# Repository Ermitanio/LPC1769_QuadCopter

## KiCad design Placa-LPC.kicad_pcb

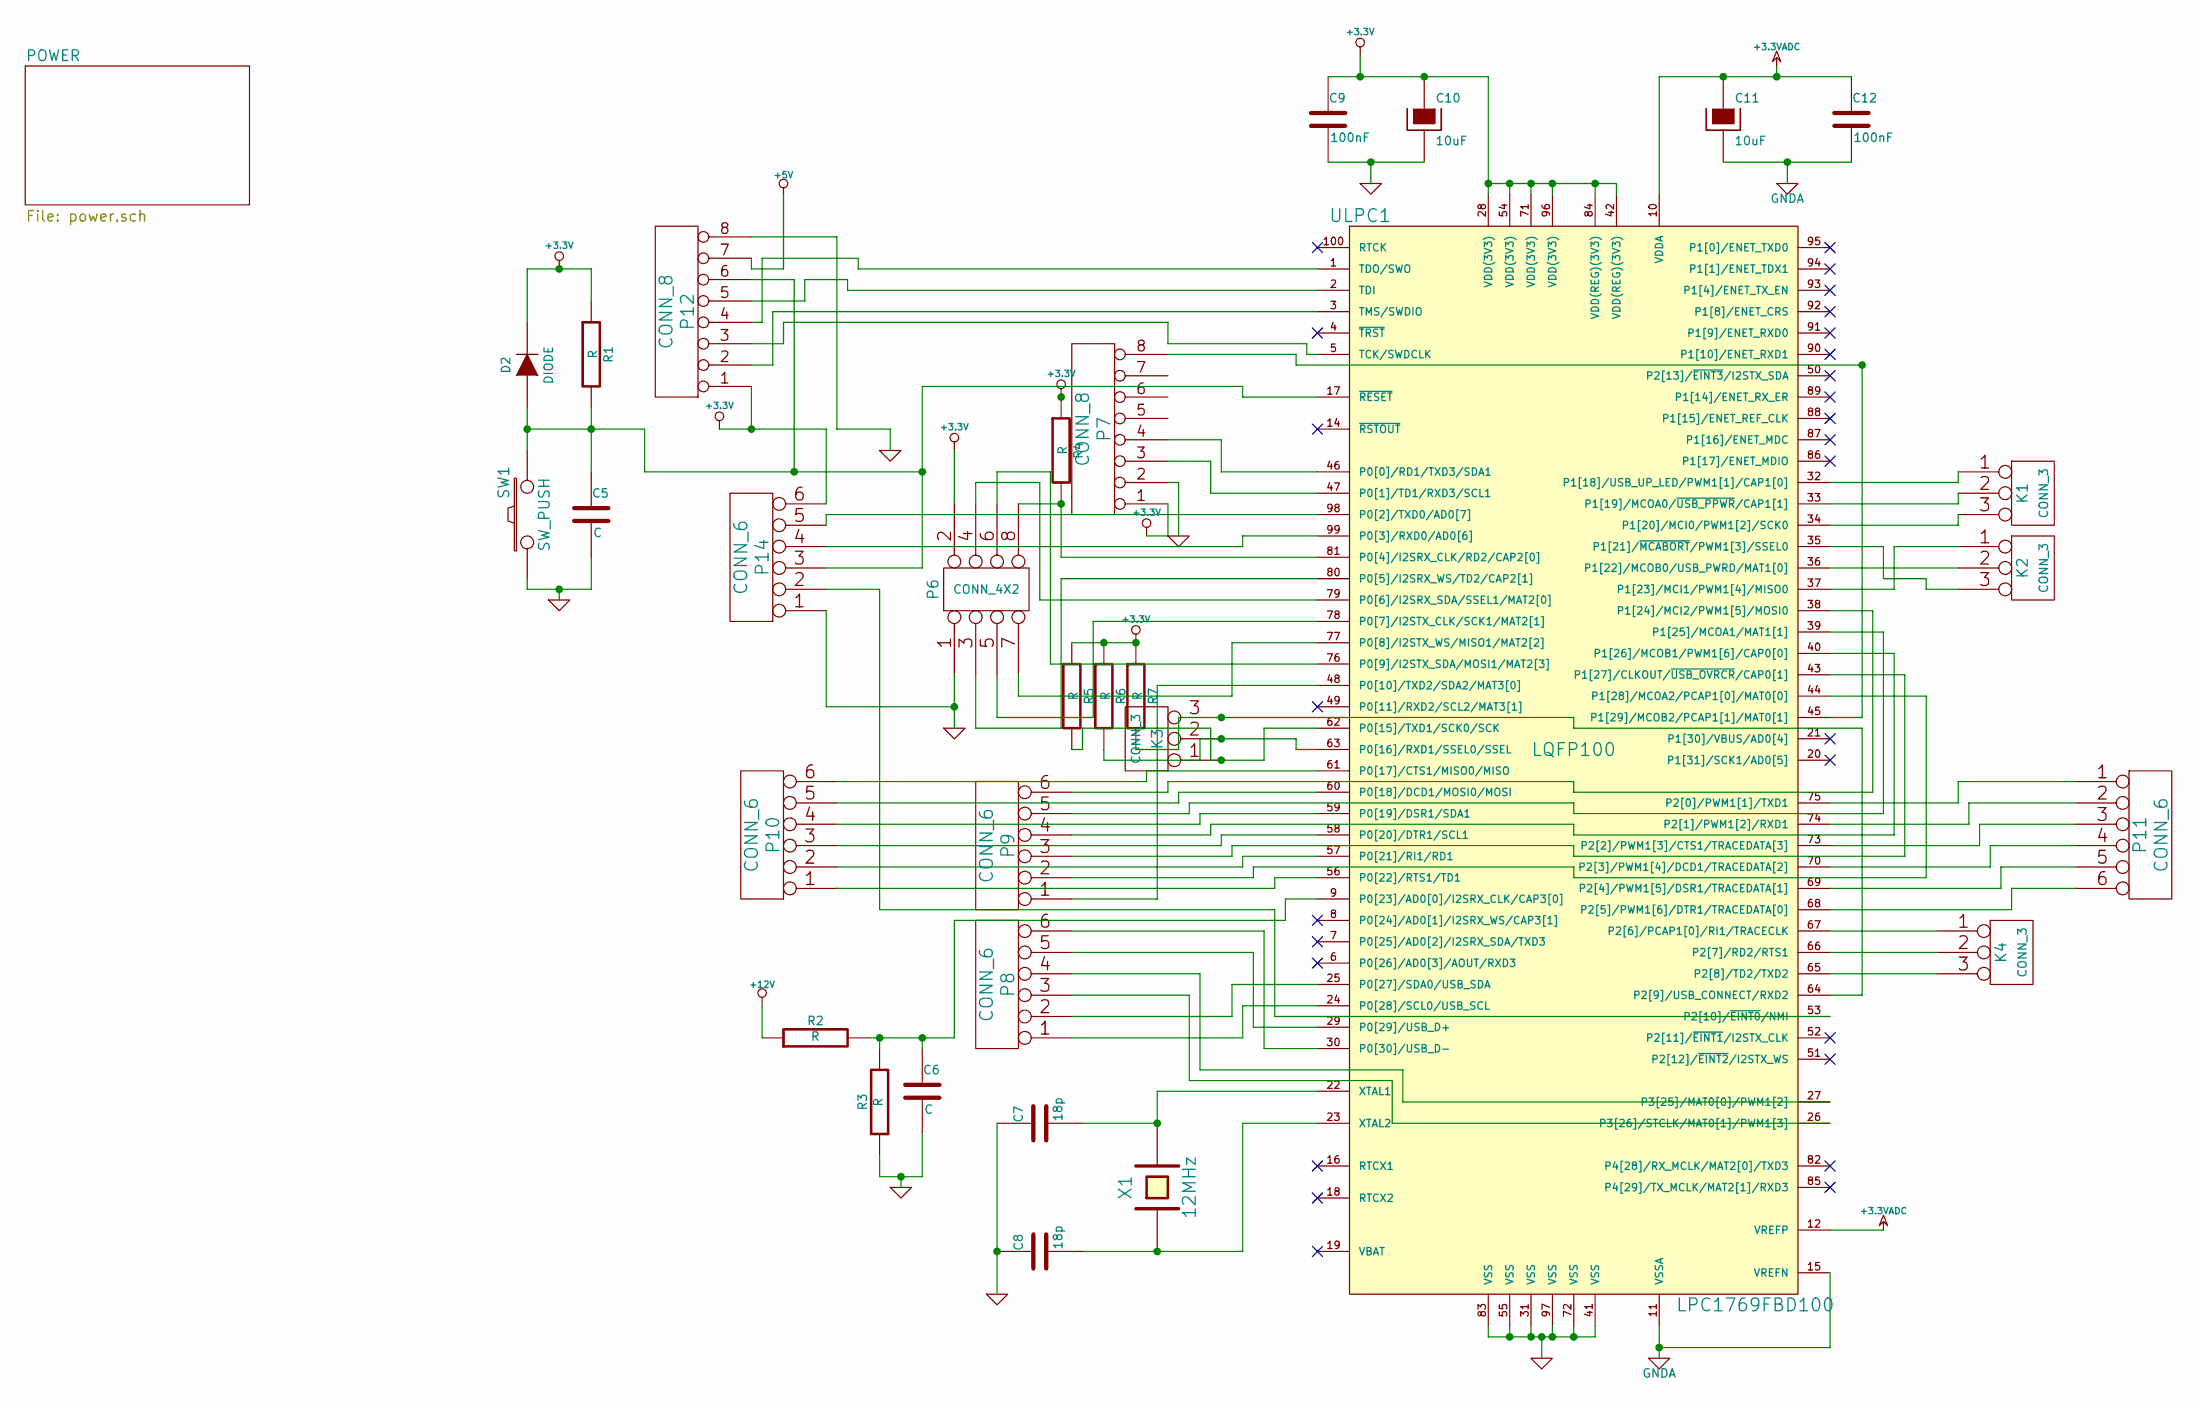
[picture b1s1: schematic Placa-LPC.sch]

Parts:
C5, C6: C
C7, C8: 18p
C9, C12: 100nF
C10, C11: 10uF
D2: DIODE
K1, K2, K3, K4: CONN_3
P6: CONN_4X2
P7, P12: CONN_8
P8, P9, P10, P11, P14: CONN_6
R1, R2, R3, R4, R5, R6, R7: R
SW1: SW_PUSH
ULPC1: LPC1769FBD100; LQFP100
X1: 12MHz

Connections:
+3.3V: C9.1, C10.1, D2.2 (K), P6.2, P7.1, P12.1, P14.6, R1.1, R4.1, R5.1, R6.1, R7.1, ULPC1.28 (VDD(3V3)), ULPC1.42 (VDD(REG)(3V3)), ULPC1.54 (VDD(3V3)), ULPC1.71 (VDD(3V3)), ULPC1.84 (VDD(REG)(3V3)), ULPC1.96 (VDD(3V3)); also elsewhere on the board
+3.3VADC: C11.1, C12.1, ULPC1.10 (VDDA), ULPC1.12 (VREFP); also elsewhere on the board
+5V: P12.7; also elsewhere on the board
+12V: R2.1; also elsewhere on the board
GND: C5.2, C6.2, C7.1, C8.1, C9.2, C10.2, P6.1, P7.2, P12.8, P14.1, R3.1, SW1.1, SW1.3, ULPC1.31 (VSS), ULPC1.41 (VSS), ULPC1.55 (VSS), ULPC1.72 (VSS), ULPC1.83 (VSS), ULPC1.97 (VSS); also elsewhere on the board
GNDA: C11.2, C12.2, ULPC1.11 (VSSA), ULPC1.15 (VREFN); also elsewhere on the board
unnamed: K1.2 (PM), ULPC1.33 (P1[19]/MCOA0/~USB_PPWR~/CAP1[1])
unnamed: K2.1, ULPC1.37 (P1[23]/MCI1/PWM1[4]/MISO0)
unnamed: K2.2 (PM), ULPC1.36 (P1[22]/MCOB0/USB_PWRD/MAT1[0])
unnamed: K2.3, ULPC1.35 (P1[21]/~MCABORT~/PWM1[3]/SSEL0)
unnamed: K1.3, ULPC1.34 (P1[20]/MCI0/PWM1[2]/SCK0)
unnamed: K1.1, ULPC1.32 (P1[18]/USB_UP_LED/PWM1[1]/CAP1[0])
unnamed: P8.6, ULPC1.30 (P0[30]/USB_D-)
unnamed: P8.5, ULPC1.29 (P0[29]/USB_D+)
unnamed: P9.5, ULPC1.39 (P1[25]/MCOA1/MAT1[1])
unnamed: P9.4, ULPC1.40 (P1[26]/MCOB1/PWM1[6]/CAP0[0])
unnamed: P9.6, ULPC1.38 (P1[24]/MCI2/PWM1[5]/MOSI0)
unnamed: P10.1, ULPC1.56 (P0[22]/RTS1/TD1)
unnamed: P9.3, ULPC1.43 (P1[27]/CLKOUT/~USB_OVRCR~/CAP0[1])
unnamed: P7.8, ULPC1.45 (P1[29]/MCOB2/PCAP1[1]/MAT0[1])
unnamed: P10.2, ULPC1.57 (P0[21]/RI1/RD1)
unnamed: P8.4, ULPC1.27 (P3[25]/MAT0[0]/PWM1[2])
unnamed: P8.3, ULPC1.26 (P3[26]/STCLK/MAT0[1]/PWM1[3])
unnamed: P12.5, ULPC1.2 (TDI)
unnamed: P12.2, ULPC1.3 (TMS/SWDIO)
unnamed: P6.6, ULPC1.76 (P0[9]/I2STX_SDA/MOSI1/MAT2[3])
unnamed: P6.7, ULPC1.77 (P0[8]/I2STX_WS/MISO1/MAT2[2])
unnamed: P7.3, ULPC1.47 (P0[1]/TD1/RXD3/SCL1)
unnamed: P7.4, ULPC1.46 (P0[0]/RD1/TXD3/SDA1)
unnamed: P6.8, R4.2, ULPC1.81 (P0[4]/I2SRX_CLK/RD2/CAP2[0])
unnamed: P9.1, ULPC1.48 (P0[10]/TXD2/SDA2/MAT3[0])
unnamed: P9.2, ULPC1.44 (P1[28]/MCOA2/PCAP1[0]/MAT0[0])
unnamed: P6.5, ULPC1.78 (P0[7]/I2STX_CLK/SCK1/MAT2[1])
unnamed: P6.4, ULPC1.79 (P0[6]/I2SRX_SDA/SSEL1/MAT2[0])
unnamed: P6.3, ULPC1.80 (P0[5]/I2SRX_WS/TD2/CAP2[1])
unnamed: P14.4, ULPC1.99 (P0[3]/RXD0/AD0[6])
unnamed: P14.2, ULPC1.53 (P2[10]/~EINT0~/NMI)
unnamed: C6.1, R2.2, R3.2, ULPC1.9 (P0[23]/AD0[0]/I2SRX_CLK/CAP3[0])
unnamed: P14.5, ULPC1.98 (P0[2]/TXD0/AD0[7])
unnamed 39: P8.1, ULPC1.24 (P0[28]/SCL0/USB_SCL); also elsewhere on the board
unnamed 40: P8.2, ULPC1.25 (P0[27]/SDA0/USB_SDA); also elsewhere on the board
unnamed: P12.4, ULPC1.1 (TDO/SWO)
unnamed: P11.5, ULPC1.69 (P2[4]/PWM1[5]/DSR1/TRACEDATA[1])
unnamed: K4.2 (PM), ULPC1.66 (P2[7]/RD2/RTS1)
unnamed: P11.6, ULPC1.68 (P2[5]/PWM1[6]/DTR1/TRACEDATA[0])
unnamed: P11.4, ULPC1.70 (P2[3]/PWM1[4]/DCD1/TRACEDATA[2])
unnamed: P11.3, ULPC1.73 (P2[2]/PWM1[3]/CTS1/TRACEDATA[3])
unnamed: P11.2, ULPC1.74 (P2[1]/PWM1[2]/RXD1)
unnamed: P10.6, ULPC1.61 (P0[17]/CTS1/MISO0/MISO)
unnamed: P10.3, ULPC1.58 (P0[20]/DTR1/SCL1)
unnamed: P10.4, ULPC1.59 (P0[19]/DSR1/SDA1)
unnamed: P10.5, ULPC1.60 (P0[18]/DCD1/MOSI0/MOSI)
unnamed: P12.3, ULPC1.5 (TCK/SWDCLK)
unnamed: C5.1, D2.1 (A), P12.6, P14.3, R1.2, SW1.2, ULPC1.17 (~RESET~)
unnamed: P11.1, ULPC1.75 (P2[0]/PWM1[1]/TXD1)
unnamed: K4.3, ULPC1.65 (P2[8]/TD2/TXD2)
unnamed: K4.1, ULPC1.67 (P2[6]/PCAP1[0]/RI1/TRACECLK)
unnamed: C8.2, ULPC1.23 (XTAL2), X1.1
unnamed: C7.2, ULPC1.22 (XTAL1), X1.2
unnamed: K3.1, R5.2, ULPC1.62 (P0[15]/TXD1/SCK0/SCK)
unnamed: K3.2 (PM), R6.2, ULPC1.63 (P0[16]/RXD1/SSEL0/SSEL)
unnamed: K3.3, R7.2, ULPC1.64 (P2[9]/USB_CONNECT/RXD2)

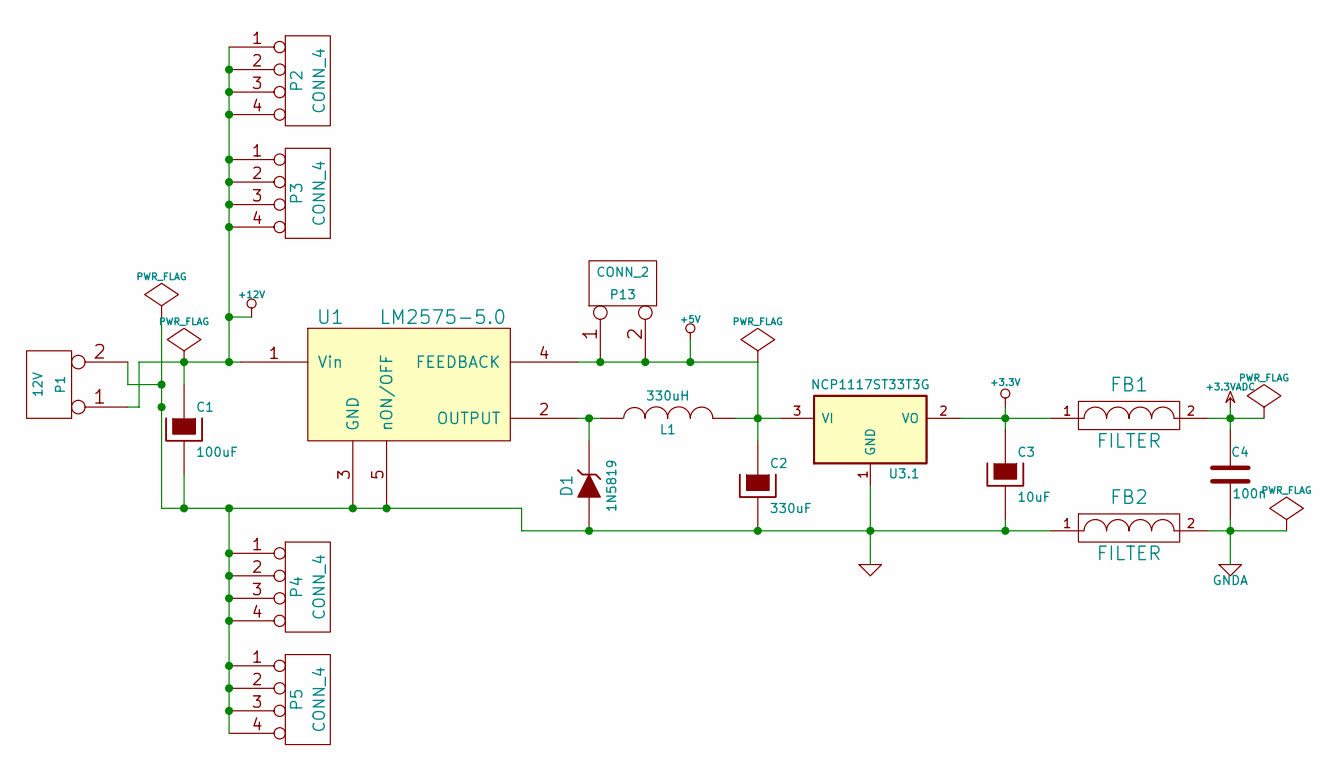
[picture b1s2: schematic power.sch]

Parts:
C1: 100uF
C2: 330uF
C3: 10uF
C4: 100n
D1: 1N5819
FB1, FB2: FILTER
L1: 330uH
P1: 12V
P2, P3, P4, P5: CONN_4
P13: CONN_2
U1: LM2575-5.0
U3.1: NCP1117ST33T3G

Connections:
+3.3V: C3.1, FB1.1, U3.1.2 (VO), U3.1.4; also elsewhere on the board
+3.3VADC: C4.1, FB1.2; also elsewhere on the board
+5V: C2.1, L1.2, P13.1, P13.2 (PM), U1.4 (FEEDBACK), U3.1.3 (VI); also elsewhere on the board
+12V: C1.1, P1.1, P2.1, P2.2, P2.3, P2.4, P3.1, P3.2, P3.3, P3.4, U1.1 (Vin); also elsewhere on the board
GND: C1.2, C2.2, C3.2, D1.1 (A), FB2.1, P1.2 (PM), P4.1, P4.2, P4.3, P4.4, P5.1, P5.2, P5.3, P5.4, U1.3 (GND), U1.5 (nON/OFF), U3.1.1 (GND); also elsewhere on the board
GNDA: C4.2, FB2.2; also elsewhere on the board
unnamed: D1.2 (K), L1.1, U1.2 (OUTPUT)

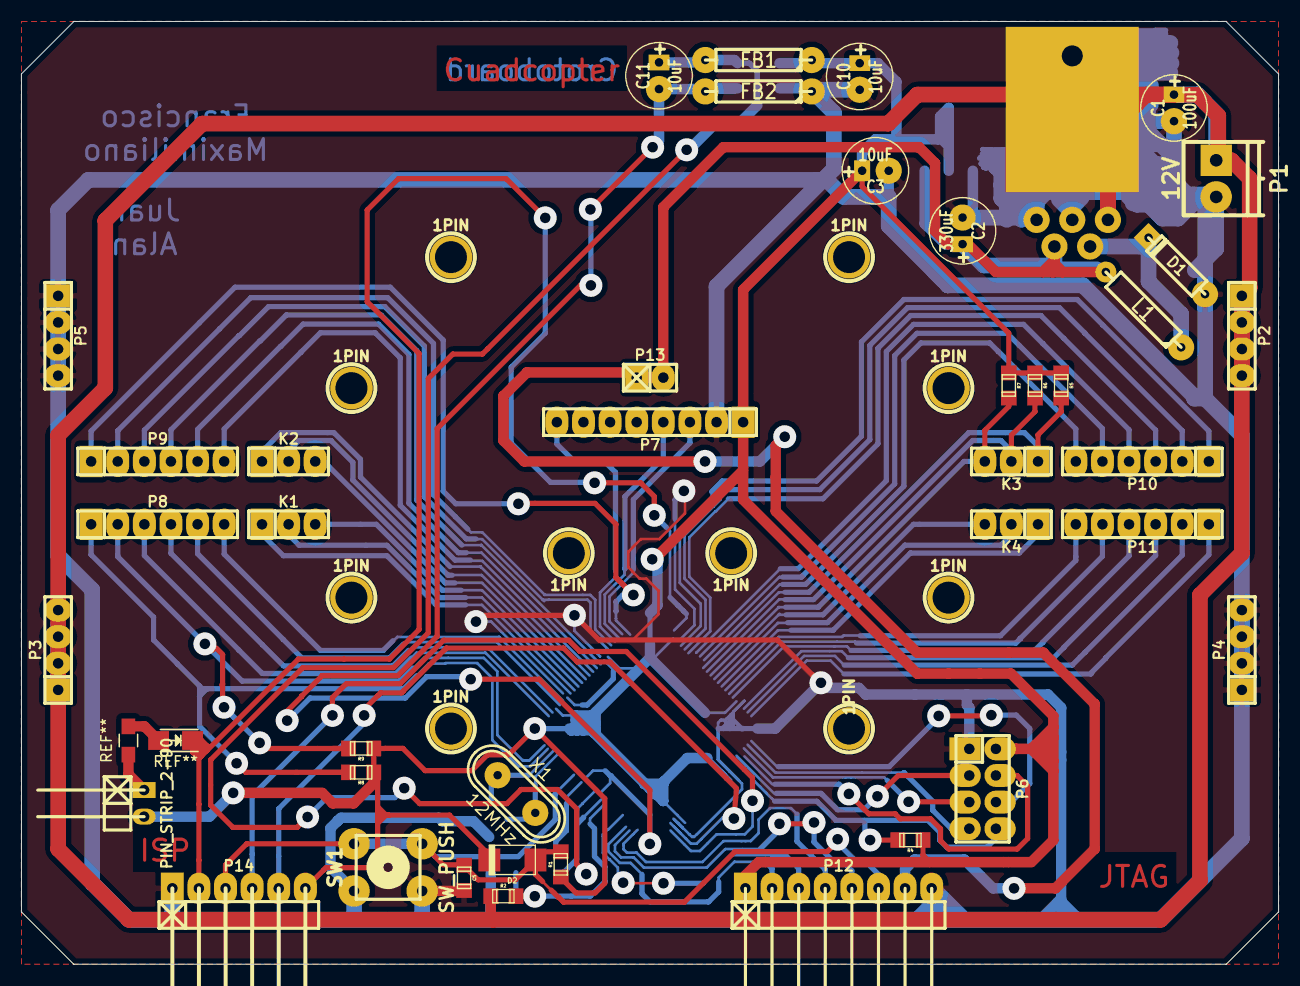
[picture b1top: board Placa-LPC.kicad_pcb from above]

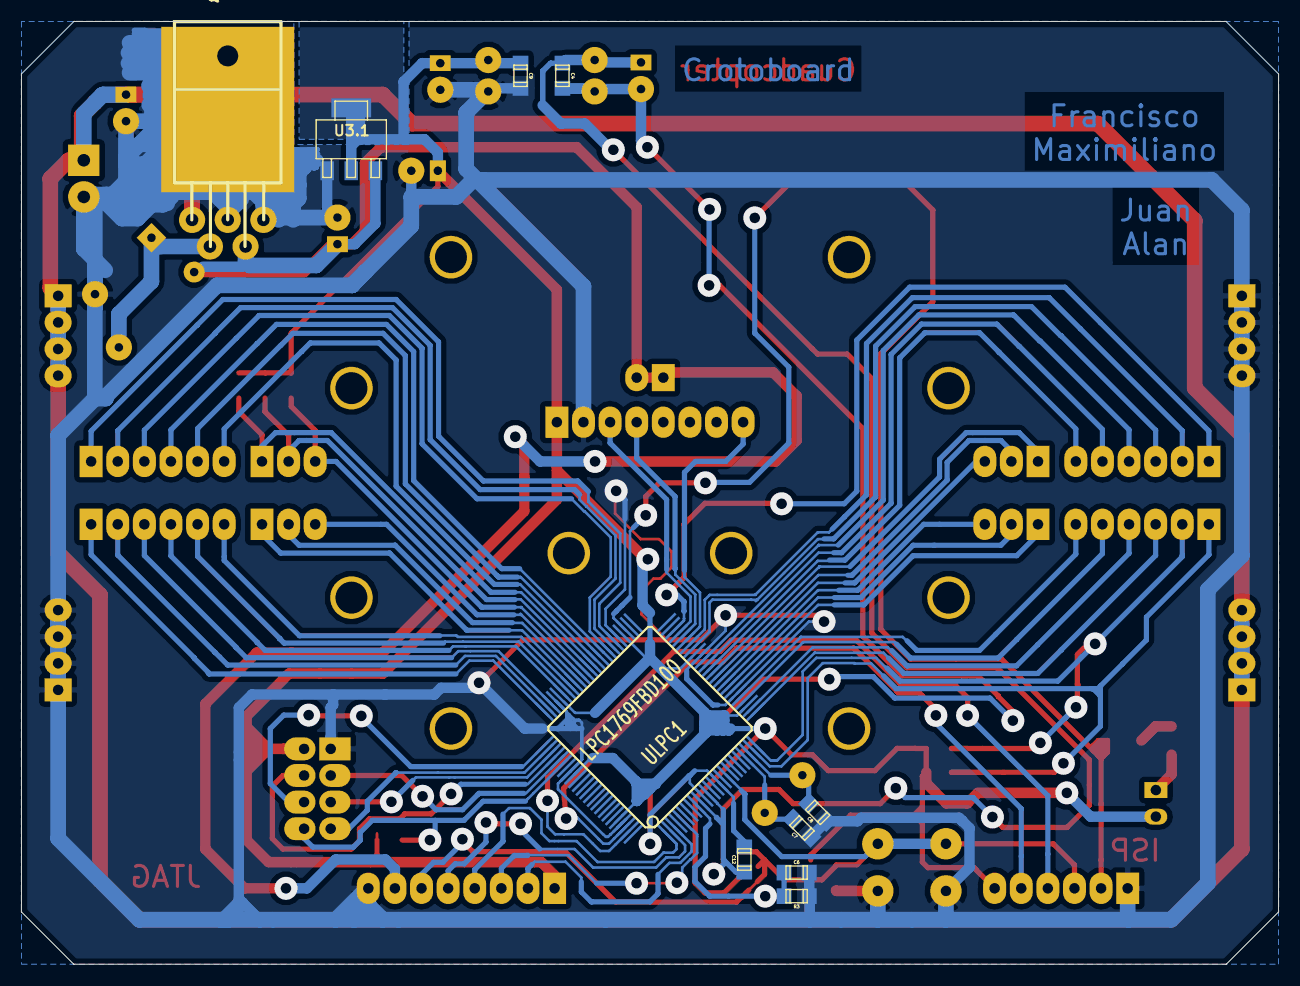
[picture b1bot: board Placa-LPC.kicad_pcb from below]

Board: 2 copper layers, 120.0 x 90.0 mm, 60 parts (10 on the bottom side), 63 nets.

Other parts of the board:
1PIN, 1PIN#2, 1PIN#3, 1PIN#4, 1PIN#5, 1PIN#6, 1PIN#7, 1PIN#8, 1PIN#9, 1PIN#10: P***; 1pin
PIN_STRIP_2-90: Val**; pin_strip_2-90
R8, R9: R; r_0805
TO220-5-horiz: Q***; to220-5-horiz

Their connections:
+3.3V: R8.1, R9.1; also elsewhere on the board
GND: TO220-5-horiz.6; also elsewhere on the board
unnamed 39: R8.2; also elsewhere on the board
unnamed 40: R9.2; also elsewhere on the board

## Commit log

2015-10-11 :space_invader: Added .gitattributes & .gitignore files
2015-10-11 Diseño kicad microcontrolador
    Diseño en progreso de la placa del lpc1769 con dimensiones del
    controlador de cuatro motores
2015-10-18 Agrego modulos
    Se agregaron las dimensiones de los modulos rf y mpu.
    Faltan definir pines y rutear
2015-10-19 Definicion de pines
    Definicion de algunos pines y ruteado de algunas pistas.
2015-10-21 Actualizado desde mi pc
2015-10-22 Ruteo pines
    Ruteo completo de pines motor y módulos.
    Falta pines programación y pines adc para batería.
    Falta definir conectores.
2015-10-22 Agregado de...
    Pines programacion jtag e isp
    Resistencias pull-up puerto cero de entrada.
    ADC para bateria y reset
2015-10-23 Version final
    Agregado de resistencias pull up y cambio de pootprint lpc
2015-10-31 Deseño Crona
2015-11-06 Ultimo diseño
    Agregado de nombres y led smd
